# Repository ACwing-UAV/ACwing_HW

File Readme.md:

<p align="center">
  <picture>
    <source media="(prefers-color-scheme: dark)" srcset="https://raw.githubusercontent.com/ACwing-UAV/ACwing/main/brand/ACwing_logo_white.png">
    
  </picture>
</p>

<h1 align="center">ACwing – open drone flight hardware</h1>

<p align="center">
  STM32WB55 flight controller, 1S power board, GNSS and optical-flow expansions<br>
  KiCad 10 · JLCPCB-ready · by Andrea Cirillo
</p>

---

ACwing is a modular set of PCBs for small multirotors. This repository is the hardware part of the
[ACwing-UAV](https://github.com/ACwing-UAV) project: the firmware is in [ACwing_FW](https://github.com/ACwing-UAV/ACwing_FW),
the mechanics in [ACwing_Mechs](https://github.com/ACwing-UAV/ACwing_Mechs), and the
[ACwing](https://github.com/ACwing-UAV/ACwing) system repository pins the versions that belong together.

The core is a **universal flight controller** that talks to its
power stage through the common **4-in-1 ESC connector** (JST SH 8-pin): on the 1S indoor mini drone it sits on the
ACwing 1S power board; on a larger 3S–6S brushless drone the same FC runs with one or two commercial 20 × 20 4-in-1
ESCs. Two optional expansion boards plug into the FC's **Qwiic** (I2C) ports: a **GNSS + compass** board for outdoor
flight and an **optical-flow + ToF** board for indoor position and height hold.

## Boards

| Board | Rev | Size | Layers | What it does | Docs | KiCad |
|---|---|---|---|---|---|---|
| **ACwing FC** | A | 40 × 40 mm, 20 × 20 holes (grommets) | 4, 1.0 mm | flight controller, 1S–6S input, up to 8 motors, BLE | [FC docs](00%20-%20Docs/00%20-%20FC_Docs/) | [project](01%20-%20FC_KiCadProj/) |
| **ACwing ESC 1S** | A | 40 × 40 mm, 20 × 20 holes | 4, 1.0 mm | 1S power board: 4 brushed motor stages, current sensor, USB-C charger | [ESC docs](00%20-%20Docs/01%20-%20ESC_1S_Docs/) | [project](02%20-%20ESC_1S_KiCadProj/) |
| **ACwing GPS** | A | 30 × 30 mm, 20 × 20 holes | 2, 1.0 mm | GNSS (u-blox SAM-M10Q) + compass, stacked above the FC | [GPS docs](00%20-%20Docs/02%20-%20GPS_Docs/) | [project](03%20-%20GPS_KiCadProj/) |
| **ACwing Flow** | A | 21 × 25 mm, 2 × M2 | 2, 1.0 mm | optical flow (PMW3901) + ToF height (VL53L1X), under the frame | [Flow docs](00%20-%20Docs/03%20-%20FLOW_Docs/) | [project](04%20-%20FLOW_KiCadProj/) |

All boards are at **rev A**: no PCB has been produced yet. The revision letter moves to B with the first
change made after a board has been built and tested.

Every board folder in `00 - Docs` holds the schematic PDF, the BoM with costing, the JLCPCB BoM and pick-and-place
files, the Gerber zip, the DRC report, the STEP model and board views.

## System

```
              ┌─────────────────────────┐   Qwiic (J3)   ┌──────────────────┐
              │      ACwing FC rev A    │───────────────▶│  ACwing GPS rev A │  optional, outdoor
  USB-C ─────▶│ STM32WB55 · IMU · baro  │                └──────────────────┘
  ELRS RX ───▶│ compass · 16 MB flash   │   Qwiic (J4)   ┌──────────────────┐
              │ BLE · 4 × RGB LED       │───────────────▶│ ACwing Flow rev A │  indoor
              └───────┬─────────┬───────┘                └──────────────────┘
          ESC link A  │         │  ESC link B (motors 5–8)
         (JST SH 8)   ▼         ▼
   ┌──────────────────────┐   ┌──────────────────────────┐
   │ ACwing ESC 1S rev A  │ or│ commercial 4-in-1 ESC(s) │
   │ 1S, brushed, charger │   │ 2S–6S, brushless         │
   └──────────────────────┘   └──────────────────────────┘
```

**Stack (1S mini drone, Mech A1):** ESC 1S hard-mounted on the frame bosses → 5 mm → FC on M2 damping grommets →
6 mm → GPS board (optional). The flow board is mounted under the battery tray, sensor side down.

The interactive stack check (every part as a prism, every connector with a mated-plug envelope; 0 clashes) is in
[`04 - System_Docs/ACwing_stack_check.html`](00%20-%20Docs/04%20-%20System_Docs/) – download the folder and open the
page locally.

## Key features

**ACwing FC rev A**
- MCU **STM32WB55CGU6** (Cortex-M4 + M0+ radio core), BLE 5 with chip antenna and ST MLPF-WB55 front end.
- Sensors: **LSM6DSV16X** IMU, **LPS22HH** barometer, **IIS2MDC** compass; **W25Q128JV** 16 MB log flash.
- Input **1S–6S** (LM5166 buck, 3–65 V; 100 % duty cycle pass-through on 1S), 4.1 V system rail, 3.1 V and 3.31 V LDOs.
- **Two ESC links** (JST SH 8-pin, standard 4-in-1 pinout): 8 motor outputs (TIM2 / TIM1 / TIM16), VBAT and current
  sense from the ESC: the FC is supplied only through ESC link A (no battery pads).
- Two Qwiic ports, ELRS / CRSF UART port, USB-C (data, DFU, bench supply), 4 × addressable RGB LEDs (XL-2020, level-shifted data), SWD pogo grid.

**ACwing ESC 1S rev A**
- 4 brushed motor stages (AON7524 N-MOSFETs) for coreless 8520 motors, 470 µF bulk capacitor.
- 2 mΩ shunt + TSC213 current sense (0.1 V/A) on the ESC link.
- USB-C 1S charger (STC4054, 455 mA) with a charge switch that keeps FC and motors off while charging.
- Battery solder pads for a JST PH 2.0 pigtail.

**ACwing GPS rev A** – u-blox **SAM-M10Q** (integrated patch antenna, I2C/DDC) and **IIS2MDC** compass away from the
motor currents; Qwiic in / out on the top side, PPS LED, backup supply.

**ACwing Flow rev A** – PixArt **PMW3901MB** flow sensor behind an **STM32C011** I2C bridge, ST **VL53L1X** ToF;
Qwiic in / out; all parts on the sensor side.

## Repository structure

```
00 - Docs/
├── 00 - FC_Docs/         FC rev A: README, pin map, schematic, BoM, JLC files, Gerber, STEP, views
├── 01 - ESC_1S_Docs/     ESC 1S rev A: same set
├── 02 - GPS_Docs/        GPS rev A: same set
├── 03 - FLOW_Docs/       Flow rev A: same set + mechanical DXF
└── 04 - System_Docs/     mechanical handoff, preliminary-draft frame answer and reply, stack check (3D page and render)
01 - FC_KiCadProj/        KiCad project, library, 3D models, generator scripts
02 - ESC_1S_KiCadProj/
03 - GPS_KiCadProj/
04 - FLOW_KiCadProj/
```

Logos, silkscreen logo footprints and the brand and silkscreen tools are in
[`brand/`](https://github.com/ACwing-UAV/ACwing/tree/main/brand) of the ACwing system repository; each board keeps
a copy of the logo footprints it uses in its own project library.

## Ordering (JLCPCB)

For each board, from its docs folder:
1. Upload `<board>_gerber.zip` (1.0 mm FR-4; 4 layers for FC and ESC, 2 layers for GPS and Flow).
2. Enable assembly and upload `<board>_BoM_JLCPCB.xlsx` and `<board>_CPL.xlsx`. Every BoM line carries its LCSC part
   number; the CPL already includes the rotation corrections. Check the pin-1 marks in the JLC preview as listed in the
   board README ("To check before ordering").

Indicative component cost per board (10 / 100 boards, components only): FC 29.4 / 24.6 USD, ESC 1S 6.4 / 5.1 USD,
GPS 27.6 / 23.4 USD, Flow 11.1 / 9.4 USD. Check LCSC stock before ordering.

## Status

**Update 2026-11-08 (still rev A):** **all tracks on all four boards at 0 / 45 / 90°** (house routing rule; tool in
[`tools/route45`](tools/route45/)); FC battery pads J7 / J8 removed (the FC is supplied through ESC link A J2 pin 2 only);
ESC 1S J1 moved 0.77 mm to the front edge, the same edge distance as FC J2. See the
[mechanical handoff](00%20-%20Docs/04%20-%20System_Docs/ACwing_mechanical_handoff.md) §0.20. ESC 1S battery pads side by side across the rear-left corner. All
boards checked and saved with KiCad 10.0.6, all outputs, renders and the stack check page regenerated.

**Update 2026-11-07 evening (still rev A):** all boards **1.0 mm** again (JLC04101H-7628 on the 4-layer boards); FC ESC A
moved to the front-left, right above ESC 1S J1 (straight cable), ESC B to the old ESC A place; FC RGB LEDs at the corner tips
(same arrangement front and rear), battery pads and BLE antenna lower on the left edge, magnetometer and barometer right of
the MCU; ESC 1S charge port moved under the FC USB-C at the rear-right chamfer. See the [mechanical handoff](00%20-%20Docs/04%20-%20System_Docs/ACwing_mechanical_handoff.md) §0.19.

**Update 2026-11-07 (still rev A, superseded):** all boards **1.6 mm** thick (JLC04161H-7628 on the 4-layer boards, 1.51 mm core
on the 2-layer boards), KiCad 10 project files, outputs regenerated with KiCad 10; stack +1.8 mm, boards +4.2 g
(indoor set) / +5.2 g with the GPS. See the [mechanical handoff](00%20-%20Docs/04%20-%20System_Docs/ACwing_mechanical_handoff.md) §0.15.

**Update 2026-11-03 (still rev A):** plated M2 mounting holes with a GND copper ring on the ESC 1S, GPS and Flow
boards (as the FC); Flow SWD test pads moved to the back side (top edge, short SWD lines) and re-routed; silkscreen as edited by A. Cirillo.

**Update 2026-11-06 (still rev A):** ESC 1S link connector J1 moved to the front edge, under FC J2 (short ESC cable);
stack check of all inter-board cables in the [mechanical handoff](00%20-%20Docs/04%20-%20System_Docs/ACwing_mechanical_handoff.md) §0.14; new realistic renders of every board and of the stack.

**Layout and routing update 2026-11-02 (still rev A):** both FC ESC links on the front edge (ESC A next to ESC B,
ELRS moved to the rear edge); Qwiic IN / OUT on one edge on every board (GPS right edge, Flow top edge); no via in any
SMD pad (exposed thermal pads excepted); fine-pitch pads resized so every pad gap is ≥ 0.19 mm (JLCPCB mask dam),
board mask expansion 0.05 mm / minimum web 0.09 mm; CSP / BGA pads 0.25 mm; FC test pads TP1–TP8 in ascending order;
Flow test pads along the perimeter, symmetric; silkscreen reduced to connector labels, logos and board names. Board
files are now saved by KiCad 9 (KiCad 10 since 2026-11-07).

**Layout update 2026-10-24 (still rev A):** FC microcontroller at the board centre, ESC link B next to the ELRS port on
the front edge, input buck moved to the left edge (no longer between the rear LEDs), LED supply kept away from the
magnetometer (EMI check in the FC README); GPS Qwiic J1 aligned with FC J3.

All four boards are routed with **0 DRC violations and 0 unconnected pads** (KiCad 10, 2026-11-07). They are not built and tested
yet: see each board README for the bench checks planned before the first order (ERC in KiCad 8/9, power-stage tests,
land patterns to verify). Firmware: [ACwing_FW](https://github.com/ACwing-UAV/ACwing_FW).

## License

The ACwing hardware is open hardware, licensed under the
[CERN Open Hardware Licence Version 2 – Strongly Reciprocal](LICENSE) (**CERN-OHL-S-2.0**).
This covers the KiCad projects, schematics, layouts, Gerbers, BoMs, STEP models, renders and documentation.
The scripts in `tools/` and `99 - Tools/` are licensed under the [GNU GPL v3.0 or later](LICENSE-GPL-3.0).

You may use, study, modify, make and sell the boards. If you distribute modified designs, or products made from
them, you must make the modified sources available under the same licence.

Source location: <https://github.com/ACwing-UAV/ACwing_HW>

The ACwing name and logo identify the original project: you may keep them on unmodified boards, but please remove
them from modified designs so they are not mistaken for official ACwing hardware.

## Author

**Andrea Cirillo** – ACwing hardware design.

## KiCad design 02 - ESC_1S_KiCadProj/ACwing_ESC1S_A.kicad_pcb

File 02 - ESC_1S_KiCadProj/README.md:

# ACwing ESC 1S rev A – KiCad project

**Project:** ACwing · **Author:** Andrea Cirillo

KiCad sources of the ACwing ESC 1S rev A board (KiCad 10 project files, 2026-11-07). The board description, schematic PDF, BoM,
JLCPCB files, Gerber, STEP and board views are in [`00 - Docs/01 - ESC_1S_Docs`](../00%20-%20Docs/01%20-%20ESC_1S_Docs/).

| File / folder | What |
|---|---|
| `ACwing_ESC1S_A.kicad_pro`, `.kicad_sch`, `.kicad_pcb` | project, schematic, routed PCB |
| `*.kicad_sym`, `*.pretty/`, `fp-lib-table`, `sym-lib-table` | project library (symbols, footprints, ACwing logos) |
| `3d/` | STEP models, referenced as `${KIPRJMOD}/3d/...` |
| `generator/` | scripts that generated, routed and checked the design (build_all_esc.sh) |

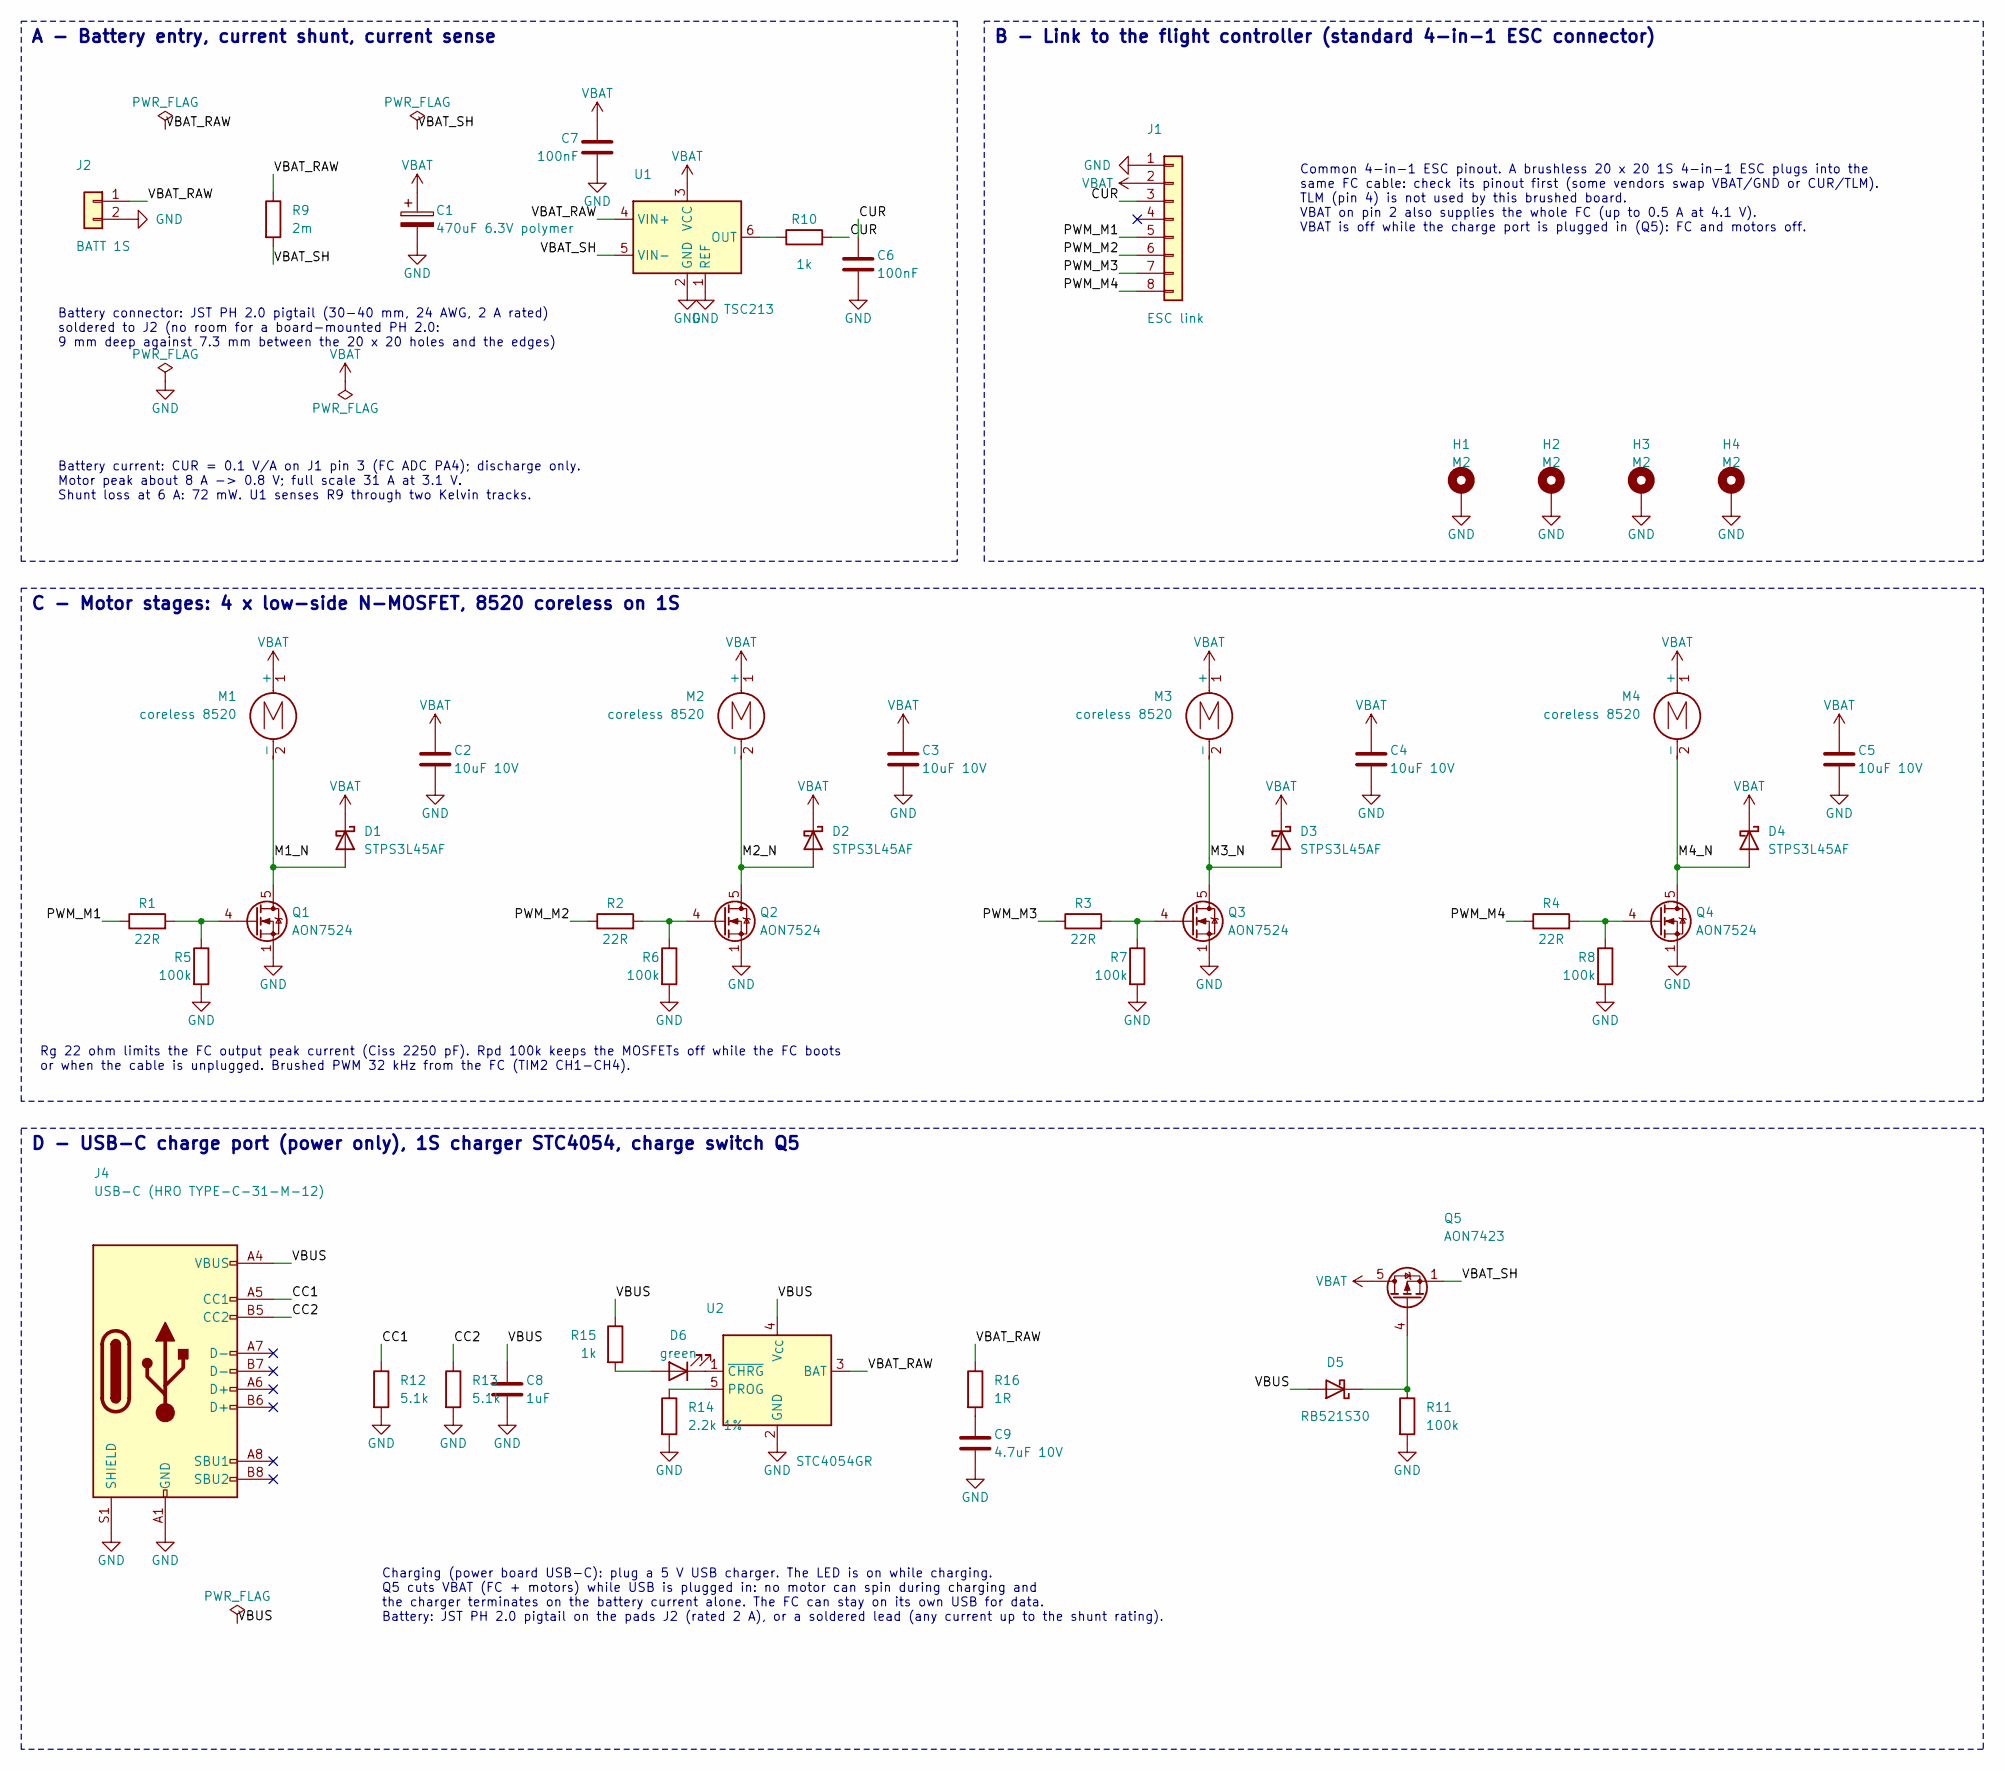
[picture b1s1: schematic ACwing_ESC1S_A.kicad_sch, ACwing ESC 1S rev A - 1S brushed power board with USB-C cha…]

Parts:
C1: 470uF 6.3V polymer; CP_EIA-7343-31_Kemet-D
C2, C3, C4, C5: 10uF 10V; C_0603_1608Metric
C6, C7: 100nF; C_0402_1005Metric
C8: 1uF; C_0402_1005Metric
C9: 4.7uF 10V; C_0603_1608Metric
D1, D2, D3, D4: STPS3L45AF; D_SMAflat
D5: RB521S30; D_SOD-523
D6: green; LED_0402_1005Metric
H1, H2, H3, H4: M2; MountingHole_PTH_2.2mm_M2_Pad3.6mm
J1: ESC link; JST_SH_SM08B-SRSS-TB_1x08-1MP_P1.00mm_Horizontal
J2: BATT 1S; BattPads_1x02_SMD
J4: USB-C (HRO TYPE-C-31-M-12); USB_C_Receptacle_HRO_TYPE-C-31-M-12
M1, M2, M3, M4: coreless 8520; MotorPads_1x02_SMD
Q1, Q2, Q3, Q4: AON7524; Vishay_PowerPAK_1212-8_Single
Q5: AON7423; Vishay_PowerPAK_1212-8_Single
R1, R2, R3, R4: 22R; R_0402_1005Metric
R5, R6, R7, R8, R11: 100k; R_0402_1005Metric
R9: 2m; R_1206_3216Metric
R10, R15: 1k; R_0402_1005Metric
R12, R13: 5.1k; R_0402_1005Metric
R14: 2.2k 1%; R_0402_1005Metric
R16: 1R; R_0402_1005Metric
U1: TSC213; SOT-363_SC-70-6
U2: STC4054GR; TSOT-23-5

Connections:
CC1: J4.A5 (CC1), R12.1
CC2: J4.B5 (CC2), R13.1
CUR: C6.1, J1.3, R10.2
GND: C1.2, C2.2, C3.2, C4.2, C5.2, C6.2, C7.2, C8.2, C9.2, H1.1, H2.1, H3.1, H4.1, J1.1, J2.2, J4.A1 (GND), J4.A12 (GND), J4.B1 (GND), J4.B12 (GND), J4.S1 (SHIELD), Q1.1 (S), Q1.2 (S), Q1.3 (S), Q2.1 (S), Q2.2 (S), Q2.3 (S), Q3.1 (S), Q3.2 (S), Q3.3 (S), Q4.1 (S), Q4.2 (S), Q4.3 (S), R5.2, R6.2, R7.2, R8.2, R11.2, R12.2, R13.2, R14.2, U1.1 (REF), U1.2 (GND), U2.2 (GND)
M1_N: D1.2 (A), M1.2 (-), Q1.5 (D)
M2_N: D2.2 (A), M2.2 (-), Q2.5 (D)
M3_N: D3.2 (A), M3.2 (-), Q3.5 (D)
M4_N: D4.2 (A), M4.2 (-), Q4.5 (D)
unnamed: C9.1, R16.2
unnamed: D5.1 (K), Q5.4 (G), R11.1
unnamed: D6.2 (A), R15.2
unnamed: D6.1 (K), U2.1 (~CHRG)
unnamed: Q1.4 (G), R1.2, R5.1
unnamed: Q2.4 (G), R2.2, R6.1
unnamed: Q3.4 (G), R3.2, R7.1
unnamed: Q4.4 (G), R4.2, R8.1
unnamed: R10.1, U1.6 (OUT)
unnamed: R14.1, U2.5 (PROG)
PWM_M1: J1.5, R1.1
PWM_M2: J1.6, R2.1
PWM_M3: J1.7, R3.1
PWM_M4: J1.8, R4.1
VBAT: C1.1, C2.1, C3.1, C4.1, C5.1, C7.1, D1.1 (K), D2.1 (K), D3.1 (K), D4.1 (K), J1.2, M1.1 (+), M2.1 (+), M3.1 (+), M4.1 (+), Q5.5 (D), U1.3 (VCC)
VBAT_RAW: J2.1, R9.1, R16.1, U1.4 (VIN+), U2.3 (BAT)
VBAT_SH: Q5.1 (S), Q5.2 (S), Q5.3 (S), R9.2, U1.5 (VIN-)
VBUS: C8.1, D5.2 (A), J4.A4 (VBUS), J4.A9 (VBUS), J4.B4 (VBUS), J4.B9 (VBUS), R15.1, U2.4 (V_{CC})

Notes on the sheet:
Common 4-in-1 ESC pinout. A brushless 20 x 20 1S 4-in-1 ESC plugs into the same FC cable: check its pinout first (some vendors swap VBAT/GND or CUR/TLM). TLM (pin 4) is not used by this brushed board. VBAT on pin 2 also supplies the whole FC (up to 0.5 A at 4.1 V). VBAT is off while the charge port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
C - Motor stages: 4 x low-side N-MOSFET, 8520 coreless on 1S
Charging (power board USB-C): plug a 5 V USB charger. The LED is on while charging. Q5 cuts VBAT (FC + motors) while USB is plugged in: no motor can spin during charging and the charger terminates on the battery current alone. The FC can stay on its own USB for data. Battery: JST PH 2.0 pigtail on 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
Battery connector: JST PH 2.0 pigtail (30-40 mm, 24 AWG, 2 A rated) soldered to J2 (no room for a board-mounted PH 2.0: 9 mm deep against 7.3 mm between the 20 x 20 holes and the edges)
Battery current: CUR = 0.1 V/A on J1 pin 3 (FC ADC PA4); discharge only. Motor peak about 8 A -> 0.8 V; full scale 31 A at 3.1 V. Shunt loss at 6 A: 72 mW. U1 senses R9 through two Kelvin tracks.
D - USB-C charge port (power only), 1S charger STC4054, charge switch Q5
A - Battery entry, current shunt, current sense
Rg 22 ohm limits the FC output peak current (Ciss 2250 pF). Rpd 100k keeps the MOSFETs off while the FC boots or when the cable is unplugged. Brushed PWM 32 kHz from the FC (TIM2 CH1-CH4).
B - Link to the flight controller (standard 4-in-1 ESC connector)

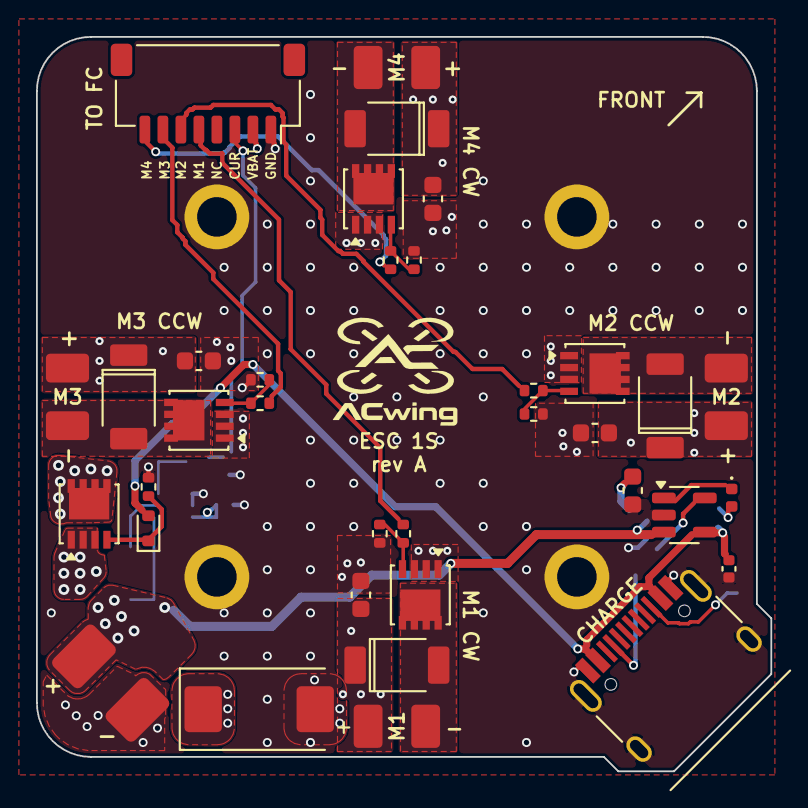
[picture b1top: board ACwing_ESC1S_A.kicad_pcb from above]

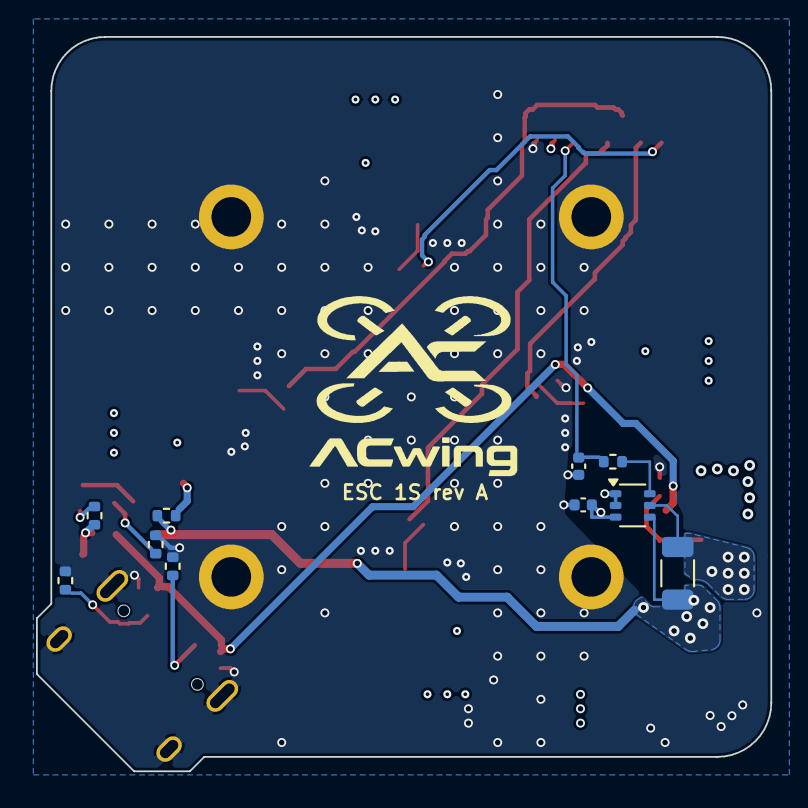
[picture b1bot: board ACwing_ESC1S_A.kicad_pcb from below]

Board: 4 copper layers, 40.8 x 40.8 mm, 51 parts (11 on the bottom side), 26 nets.

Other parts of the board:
LOGO1: ACwing_Logo_Full_6mm
LOGO2: ACwing_Logo_Full_10mm

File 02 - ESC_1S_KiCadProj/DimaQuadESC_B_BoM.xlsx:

DimaQuadESC rev B - assembly BoM (1 board)
Source: DimaQuadESC_B.kicad_sch / DimaQuadESC_B.kicad_pcb. LCSC part numbers fr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
Item | Quantity | Part Reference | Value | MPN | Manufacturer | LCSC / JLCPCB # | Package | Description | Side | Notes
1 | 1 | C1 | 470uF 6.3V polymer | T520D477M006ATE015 | KEMET | C696809 | 7343-31 (EIA D), h 2.8 mm | Capacitor, tantalum polymer, 470 uF, 6.3 V, 15 mOhm | Top | Bulk at the battery entry, + to VBAT. Low LCSC stock: any 470 uF 6.3 V 7343 pol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
2 | 4 | C2, C3, C4, C5 | 10uF 10V | CL10A106KP8NNNC | Samsung Electro-Mechanics | C19702 | 0603 (1608 metric) | Capacitor, MLCC, 10 uF, 10 V, X5R | Top | Local decoupling next to each MOSFET (hot loop)
3 | 2 | C6, C7 | 100nF | CL05B104KO5NNNC | Samsung Electro-Mechanics | C1525 | 0402 (1005 metric) | Capacitor, MLCC, 100 nF, 16 V, X7R | Bottom | U1 supply (C7) and CUR filter (C6)
4 | 1 | C8 | 1uF | CL05A105KA5NQNC | Samsung Electro-Mechanics | C52923 | 0402 (1005 metric) | Capacitor, MLCC, 1 uF, 25 V, X5R | Top | Charger input (VBUS)
5 | 1 | C9 | 4.7uF 10V | CL10A475KO8NNNC | Samsung Electro-Mechanics | C19666 | 0603 (1608 metric) | Capacitor, MLCC, 4.7 uF, 16 V, X5R | Top | Charger output RC (with R16)
6 | 4 | D1, D2, D3, D4 | STPS3L45AF | SS34F | GOODWORK | C908669 | SMAF (DO-221AC) | Diode, Schottky, 40 V, 3 A, Vf 0.55 V @ 3 A | Top | Motor freewheel diode. Replaces STPS3L45AF (low LCSC stock), same DO-221AC outl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
7 | 1 | D5 | RB521S30 | RB521S30T1G | onsemi | C8523 | SOD-523 | Diode, Schottky, 30 V, 200 mA | Top | VBUS -> Q5 gate (charge switch off while charging)
8 | 1 | D6 | green | XL-1005UGC | XINGLIGHT | C965793 | 0402 (1005 metric) | LED, green 525 nm, 0402 | Top | Charge LED (on = charging), top side next to the charge port
9 | 1 | J1 | ESC link | SM08B-SRSS-TB(LF)(SN) | JST | C160407 | JST SH 8P side entry, h 2.9 mm | Connector, JST SH, 8 positions, 1.0 mm pitch, side entry | Top | ESC link to the FC: 1 GND, 2 VBAT, 3 CUR, 4 TLM (n.c.), 5-8 M1-M4. Mouth at the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
10 | 1 | J4 | USB-C (HRO TYPE-C-31-M-12) | TYPE-C-31-M-12 | HRO (Korea Hroparts) | C165948 | USB-C receptacle, 16 pin, SMD + THT shell | Connector, USB Type-C receptacle, top mount | Top | Charge port (power only), front-left chamfer
11 | 4 | Q1, Q2, Q3, Q4 | AON7524 | AON7524 | Alpha & Omega Semiconductor | C431195 | DFN 3x3 EP (DFN3x3A_8L_EP1) | MOSFET, N-channel, 30 V, 30 A, logic level | Top | Low-side motor switch, one per channel. Land pattern: Vishay PowerPAK 1212-8 (c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
12 | 1 | Q5 | AON7423 | AON7423 | Alpha & Omega Semiconductor | C99711 | DFN 3x3 EP | MOSFET, P-channel, 20 V, 50 A, 4.9 mOhm @ -2.5 V, Vgs +-8 V | Top | Charge switch Q5: board supply off while the charge port is plugged in
13 | 4 | R1, R2, R3, R4 | 22R | 0402WGF220JTCE | UNI-ROYAL | C25092 | 0402 (1005 metric) | Resistor, 22 Ohm, 5 %, 1/16 W | Top | MOSFET gate resistors
14 | 5 | R5, R6, R7, R8, R11 | 100k | 0402WGF1003TCE | UNI-ROYAL | C25741 | 0402 (1005 metric) | Resistor, 100 kOhm, 1 %, 1/16 W | Top | Gate pull-downs: MOSFETs off with the cable unplugged or the FC booting (R5-R8)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
15 | 1 | R9 | 2m | RLM12FTCMR002 | TA-I Tech | C710257 | 1206 (3216 metric) | Resistor, current sense, 2 mOhm, 1 %, 1 W | Bottom | Battery shunt, bottom side, Kelvin-connected to U1
16 | 2 | R10, R15 | 1k | 0402WGF1001TCE | UNI-ROYAL | C11702 | 0402 (1005 metric) | Resistor, 1 kOhm, 1 %, 1/16 W | Bottom | CUR filter (1k / 100 nF, 1.6 kHz) (R10); charge LED (R15)
17 | 2 | R12, R13 | 5.1k | 0402WGF5101TCE | UNI-ROYAL | C25905 | 0402 (1005 metric) | Resistor, 5.1 kOhm, 1 %, 1/16 W | Bottom | USB-C CC pull-downs (sink)
18 | 1 | R14 | 2.2k 1% | 0402WGF2201TCE | UNI-ROYAL | C25879 | 0402 (1005 metric) | Resistor, 2.2 kOhm, 1 %, 1/16 W | Bottom | Charger R_PROG: 455 mA
19 | 1 | R16 | 1R | FRC0402F1R00TS | FOJAN | C2909329 | 0402 (1005 metric) | Resistor, 1 Ohm, 1 %, 1/16 W | Bottom | Charger output RC (with C9)
20 | 1 | U1 | TSC213 | TSC213ICT | STMicroelectronics | C1858319 | SC70-6 (SOT-363) | Current-sense amplifier, gain 50 V/V, zero drift | Bottom | Battery current: CUR = 0.1 V/A on J1 pin 3
21 | 1 | U2 | STC4054GR | STC4054GR | STMicroelectronics | C262930 | TSOT-23-5 | Li-ion linear charger, 4.2 V, up to 800 mA | Top | 1S charger, 455 mA (R14 2.2k)
Total | 40 | Total placements (assembled parts) | - | 21 | line items | - | - | - | - | Not-assembled items listed below
Not assembled (PCB features / DNP)
Item | Quantity | Part Reference | Value | MPN | Manufacturer | LCSC / JLCPCB # | Package | Description | Side | Notes
NA1 | 4 | H1, H2, H3, H4 | M2 | N/A (PCB feature) | N/A | N/A | NPTH 2.2 mm | Mounting hole, M2, 20 x 20 pattern | Top | Hard mount to the frame bosses; keep-out r 2.6 mm on both sides
NA2 | 4 | M1, M2, M3, M4 | coreless 8520 | N/A (PCB feature) | N/A | N/A | MotorPads_1x02_SMD | Motor lead solder pads (8.5 x 20 mm coreless brushed motors, 3.7 V) | Top | Soldered by hand; "+" pad (silk mark) to the red/blue lead. M1/M4 CW, M2/M3 CCW
NA3 | 1 | J2 | BATT 1S | N/A (PCB feature) | N/A | N/A | BattPads_1x02_SMD | Battery lead solder pads, 1S LiPo, AWG 22-24 | Top | Rear corner; "+" silk mark on the VBAT pad
NA4 | 1 | - (soldered to J2) | JST PH 2.0 pigtail | PH 2.0 male lead, 30-40 mm, 24 AWG (any brand) | N/A | N/A | off-board | Battery plug pigtail soldered to J2 (rated 2 A) | Top | Hand-soldered: red to +. Match the polarity of the battery plug (not standardis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

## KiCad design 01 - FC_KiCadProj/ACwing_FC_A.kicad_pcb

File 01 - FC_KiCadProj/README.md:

# ACwing FC rev A – KiCad project

**Project:** ACwing · **Author:** Andrea Cirillo

KiCad sources of the ACwing FC rev A board (KiCad 10 project files, 2026-11-07). The board description, schematic PDF, BoM,
JLCPCB files, Gerber, STEP and board views are in [`00 - Docs/00 - FC_Docs`](../00%20-%20Docs/00%20-%20FC_Docs/).

| File / folder | What |
|---|---|
| `ACwing_FC_A.kicad_pro`, `.kicad_sch`, `.kicad_pcb` | project, schematic, routed PCB |
| `*.kicad_sym`, `*.pretty/`, `fp-lib-table`, `sym-lib-table` | project library (symbols, footprints, ACwing logos) |
| `3d/` | STEP models, referenced as `${KIPRJMOD}/3d/...` |
| `generator/` | scripts that generated, routed and checked the design (build_all_h.sh) |

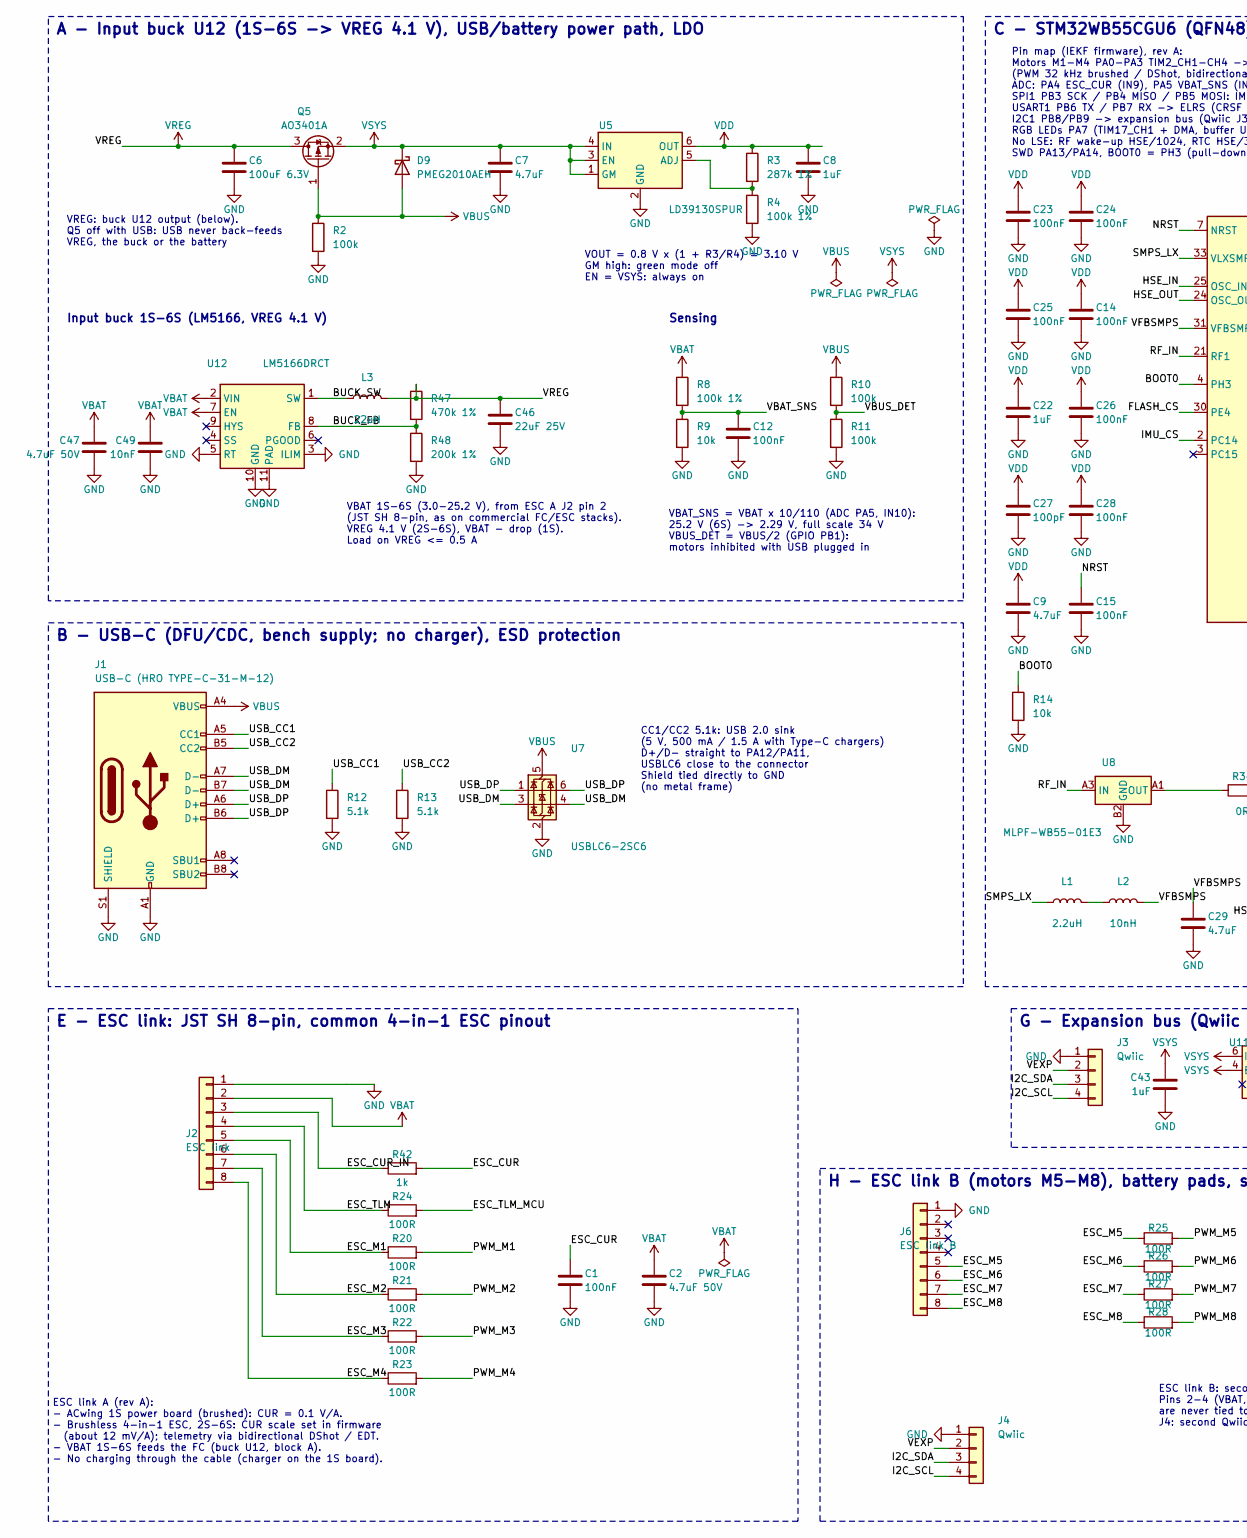
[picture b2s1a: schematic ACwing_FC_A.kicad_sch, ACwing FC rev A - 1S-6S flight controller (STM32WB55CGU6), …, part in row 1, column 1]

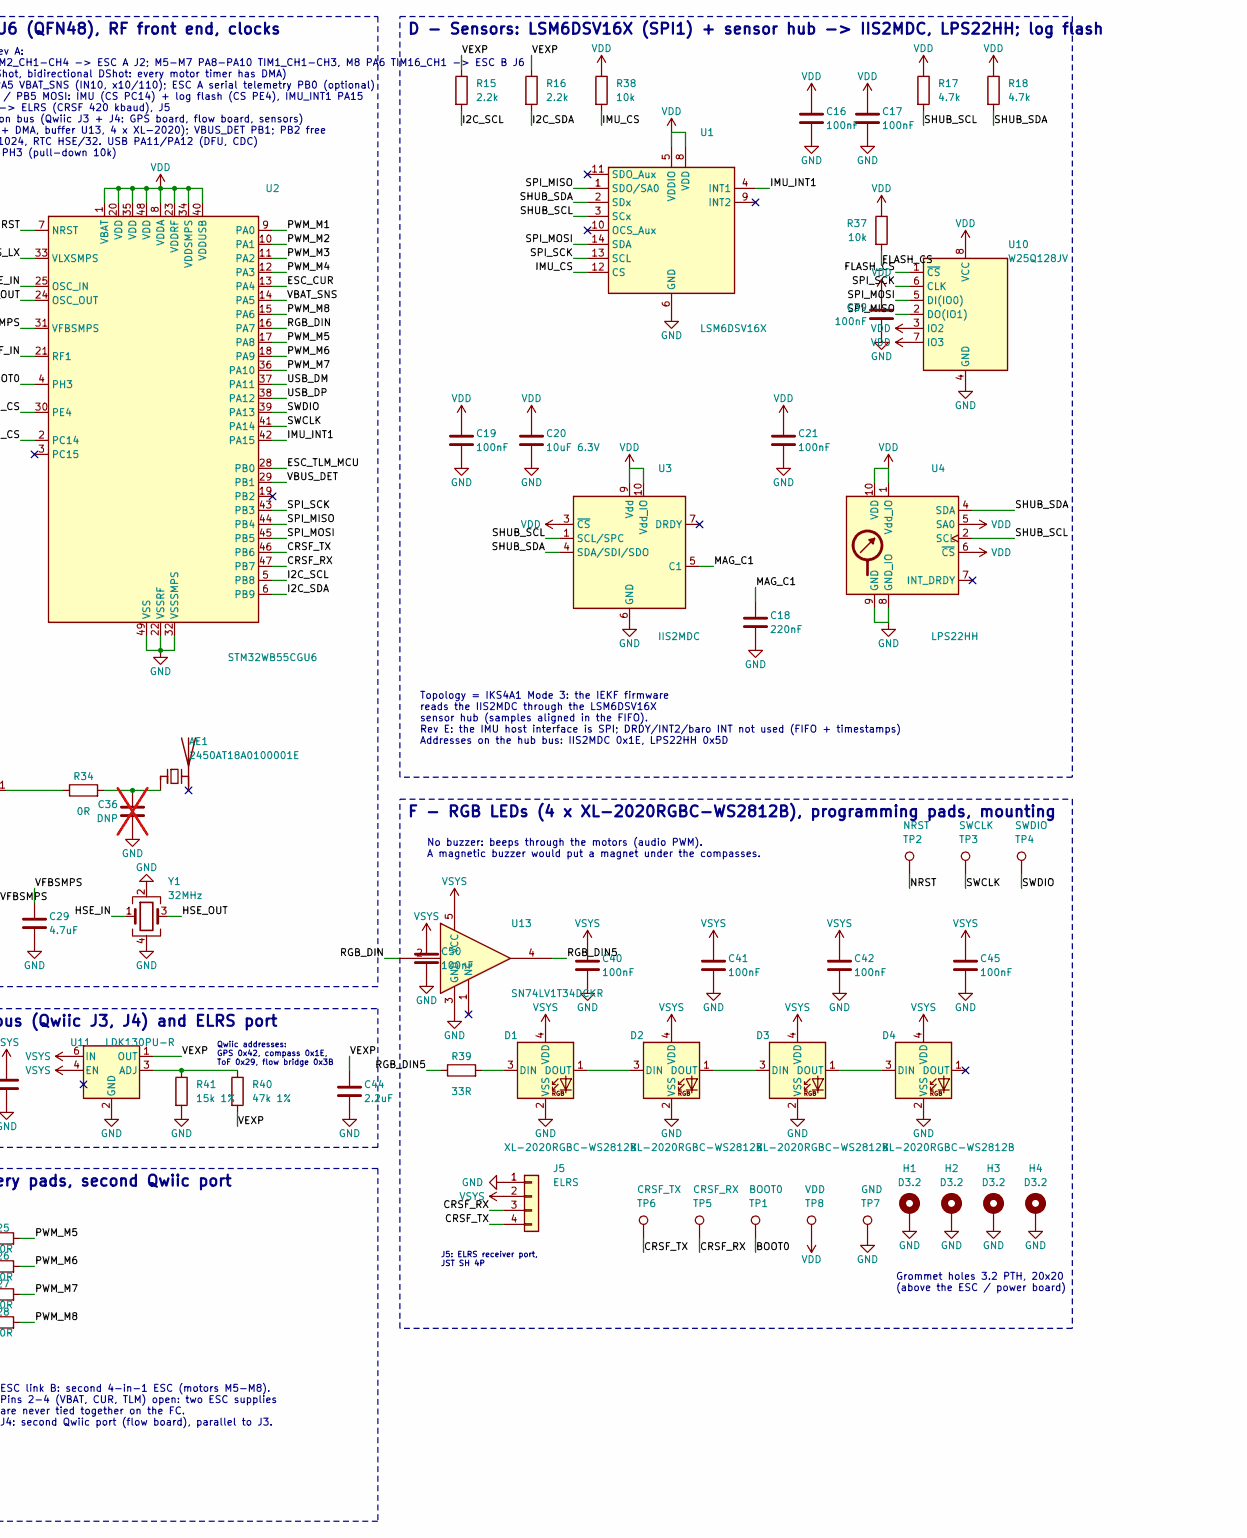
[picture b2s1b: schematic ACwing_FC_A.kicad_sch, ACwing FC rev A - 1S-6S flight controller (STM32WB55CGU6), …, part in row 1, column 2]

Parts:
AE1: 2450AT18A0100001E; Johanson_2450AT18x100
C1, C12, C14, C15, C16, C17, C19, C21, C23, C24, C25, C26, C28, C39, C40, C41, C42, C45, C50: 100nF; C_0402_1005Metric
C2, C47: 4.7uF 50V; C_1206_3216Metric
C6: 100uF 6.3V; C_1206_3216Metric
C7, C9: 4.7uF; C_0603_1608Metric
C8, C22, C43: 1uF; C_0402_1005Metric
C18: 220nF; C_0402_1005Metric
C20: 10uF 6.3V; C_0603_1608Metric
C27: 100pF; C_0402_1005Metric
C29: 4.7uF; C_0402_1005Metric
C36: DNP; C_0402_1005Metric; not fitted
C44: 2.2uF; C_0402_1005Metric
C46: 22uF 25V; C_0805_2012Metric
C49: 10nF; C_0402_1005Metric
D1, D2, D3, D4: XL-2020RGBC-WS2812B; LED_WS2812B-2020_PLCC4_2.0x2.0mm
D9: PMEG2010AEH; D_SOD-123F
H1, H2, H3, H4: D3.2; Grommet_PTH_3.2mm_Pad5.0mm
J1: USB-C (HRO TYPE-C-31-M-12); USB_C_Receptacle_HRO_TYPE-C-31-M-12
J2: ESC link; JST_SH_SM08B-SRSS-TB_1x08-1MP_P1.00mm_Horizontal
J3, J4: Qwiic; JST_SH_SM04B-SRSS-TB_1x04-1MP_P1.00mm_Horizontal
J5: ELRS; JST_SH_SM04B-SRSS-TB_1x04-1MP_P1.00mm_Horizontal
J6: ESC link B; JST_SH_SM08B-SRSS-TB_1x08-1MP_P1.00mm_Horizontal
L1: 2.2uH; L_0805_2012Metric
L2: 10nH; L_0402_1005Metric
L3: 22uH; L_Sunlord_SWPA5040S
Q5: AO3401A; SOT-23
R2, R10, R11: 100k; R_0402_1005Metric
R3: 287k 1%; R_0402_1005Metric
R4, R8: 100k 1%; R_0402_1005Metric
R9, R14, R37, R38: 10k; R_0402_1005Metric
R12, R13: 5.1k; R_0402_1005Metric
R15, R16: 2.2k; R_0402_1005Metric
R17, R18: 4.7k; R_0402_1005Metric
R20, R21, R22, R23, R24, R25, R26, R27, R28: 100R; R_0402_1005Metric
R34: 0R; R_0402_1005Metric
R39: 33R; R_0402_1005Metric
R40: 47k 1%; R_0402_1005Metric
R41: 15k 1%; R_0402_1005Metric
R42: 1k; R_0402_1005Metric
R47: 470k 1%; R_0402_1005Metric
R48: 200k 1%; R_0402_1005Metric
TP1: BOOT0; TestPoint_Pad_D1.0mm
TP2: NRST; TestPoint_Pad_D1.0mm
TP3: SWCLK; TestPoint_Pad_D1.0mm
TP4: SWDIO; TestPoint_Pad_D1.0mm
TP5: CRSF_RX; TestPoint_Pad_D1.0mm
TP6: CRSF_TX; TestPoint_Pad_D1.0mm
TP7: GND; TestPoint_Pad_D1.0mm
TP8: VDD; TestPoint_Pad_D1.0mm
U1: LSM6DSV16X; LGA-14_3x2.5mm_P0.5mm_LayoutBorder3x4y
U2: STM32WB55CGU6; QFN-48-1EP_7x7mm_P0.5mm_EP5.6x5.6mm
U3: IIS2MDC; LGA-12_2x2mm_P0.5mm
U4: LPS22HH; ST_HLGA-10_2x2mm_P0.5mm_LayoutBorder3x2y
U5: LD39130SPUR; DFN-6_1.3x1.2mm_P0.4mm
U7: USBLC6-2SC6; SOT-23-6
U8: MLPF-WB55-01E3; ST_MLPF-WB55-01E3_CSP-6
U10: W25Q128JV; WSON-8-1EP_6x5mm_P1.27mm_EP3.4x4mm
U11: LDK130PU-R; DFN-6_1.3x1.2mm_P0.4mm
U12: LM5166DRCT; Texas_DRC0010J
U13: SN74LV1T34DCKR; SOT-353_SC-70-5
Y1: 32MHz; Crystal_SMD_2016-4Pin_2.0x1.6mm

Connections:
BOOT0: R14.1, TP1.1, U2.4 (PH3)
BUCK_FB: R47.2, R48.1, U12.8 (FB)
BUCK_SW: L3.1, U12.1 (SW)
CRSF_RX: J5.3, TP5.1, U2.47 (PB7)
CRSF_TX: J5.4, TP6.1, U2.46 (PB6)
ESC_CUR: C1.1, R42.2, U2.13 (PA4)
ESC_CUR_IN: J2.3, R42.1
ESC_M1: J2.5, R20.1
ESC_M2: J2.6, R21.1
ESC_M3: J2.7, R22.1
ESC_M4: J2.8, R23.1
ESC_M5: J6.5, R25.1
ESC_M6: J6.6, R26.1
ESC_M7: J6.7, R27.1
ESC_M8: J6.8, R28.1
ESC_TLM: J2.4, R24.1
ESC_TLM_MCU: R24.2, U2.28 (PB0)
FLASH_CS: R37.2, U2.30 (PE4), U10.1 (~CS)
GND: C1.2, C2.2, C6.2, C7.2, C8.2, C9.2, C12.2, C14.2, C15.2, C16.2, C17.2, C18.2, C19.2, C20.2, C21.2, C22.2, C23.2, C24.2, C25.2, C26.2, C27.2, C28.2, C29.2, C36.2, C39.2, C40.2, C41.2, C42.2, C43.2, C44.2, C45.2, C46.2, C47.2, C49.2, C50.2, D1.2 (VSS), D2.2 (VSS), D3.2 (VSS), D4.2 (VSS), H1.1, H2.1, H3.1, H4.1, J1.A1 (GND), J1.A12 (GND), J1.B1 (GND), J1.B12 (GND), J1.S1 (SHIELD), J2.1, J3.1, J4.1, J5.1, J6.1, R2.2, R4.2, R9.2, R11.2, R12.2, R13.2, R14.2, R41.2, R48.2, TP7.1, U1.6 (GND), U1.7 (GND), U2.22 (VSSRF), U2.32 (VSSSMPS), U2.49 (VSS), U3.6 (GND), U3.8 (GND), U4.3 (GND), U4.8 (GND_IO), U4.9 (GND), U5.2 (GND), U7.2 (GND), U8.A2 (GND), U8.B1 (GND), U8.B2 (GND), U8.B3 (GND), U10.4 (GND), U11.2 (GND), U12.3 (ILIM), U12.5 (RT), U12.10 (GND), U12.11 (PAD), U13.3 (GND), Y1.2, Y1.4
HSE_IN: U2.25 (OSC_IN), Y1.1
HSE_OUT: U2.24 (OSC_OUT), Y1.3
I2C_SCL: J3.4, J4.4, R15.2, U2.5 (PB8)
I2C_SDA: J3.3, J4.3, R16.2, U2.6 (PB9)
IMU_CS: R38.2, U1.12 (CS), U2.2 (PC14)
IMU_INT1: U1.4 (INT1), U2.42 (PA15)
MAG_C1: C18.1, U3.5 (C1)
NRST: C15.1, TP2.1, U2.7 (NRST)
unnamed: AE1.1 (FEED), C36.1, R34.2
unnamed: D1.3 (DIN), R39.2
unnamed: D1.1 (DOUT), D2.3 (DIN)
unnamed: D2.1 (DOUT), D3.3 (DIN)
unnamed: D3.1 (DOUT), D4.3 (DIN)
unnamed: L1.2, L2.1
unnamed: R3.2, R4.1, U5.5 (ADJ)
unnamed: R34.1, U8.A1 (OUT)
unnamed: R40.1, R41.1, U11.3 (ADJ)
PWM_M1: R20.2, U2.9 (PA0)
PWM_M2: R21.2, U2.10 (PA1)
PWM_M3: R22.2, U2.11 (PA2)
PWM_M4: R23.2, U2.12 (PA3)
PWM_M5: R25.2, U2.17 (PA8)
PWM_M6: R26.2, U2.18 (PA9)
PWM_M7: R27.2, U2.36 (PA10)
PWM_M8: R28.2, U2.15 (PA6)
RF_IN: U2.21 (RF1), U8.A3 (IN)
RGB_DIN: U2.16 (PA7), U13.2
RGB_DIN5: R39.1, U13.4
SHUB_SCL: R17.2, U1.3 (SCx), U3.1 (SCL/SPC), U4.2 (SCL)
SHUB_SDA: R18.2, U1.2 (SDx), U3.4 (SDA/SDI/SDO), U4.4 (SDA)
SMPS_LX: L1.1, U2.33 (VLXSMPS)
SPI_MISO: U1.1 (SDO/SA0), U2.44 (PB4), U10.2 (DO(IO1))
SPI_MOSI: U1.14 (SDA), U2.45 (PB5), U10.5 (DI(IO0))
SPI_SCK: U1.13 (SCL), U2.43 (PB3), U10.6 (CLK)
SWCLK: TP3.1, U2.41 (PA14)
SWDIO: TP4.1, U2.39 (PA13)
USB_CC1: J1.A5 (CC1), R12.1
USB_CC2: J1.B5 (CC2), R13.1
USB_DM: J1.A7 (D-), J1.B7 (D-), U2.37 (PA11), U7.3 (I/O2), U7.4 (I/O2)
USB_DP: J1.A6 (D+), J1.B6 (D+), U2.38 (PA12), U7.1 (I/O1), U7.6 (I/O1)
VBAT: C2.1, C47.1, C49.1, J2.2, R8.1, U12.2 (VIN), U12.7 (EN)
VBAT_SNS: C12.1, R8.2, R9.1, U2.14 (PA5)
VBUS: D9.2 (A), J1.A4 (VBUS), J1.A9 (VBUS), J1.B4 (VBUS), J1.B9 (VBUS), Q5.1 (G), R2.1, R10.1, U7.5 (VBUS)
VBUS_DET: R10.2, R11.1, U2.29 (PB1)
VDD: C8.1, C9.1, C14.1, C16.1, C17.1, C19.1, C20.1, C21.1, C22.1, C23.1, C24.1, C25.1, C26.1, C27.1, C28.1, C39.1, R3.1, R17.1, R18.1, R37.1, R38.1, TP8.1, U1.5 (VDDIO), U1.8 (VDD), U2.1 (VBAT), U2.8 (VDDA), U2.20 (VDD), U2.23 (VDDRF), U2.34 (VDDSMPS), U2.35 (VDD), U2.40 (VDDUSB), U2.48 (VDD), U3.3 (~CS), U3.9 (Vdd), U3.10 (Vdd_IO), U4.1 (Vdd_IO), U4.5 (SA0), U4.6 (~CS), U4.10 (VDD), U5.6 (OUT), U10.3 (IO2), U10.7 (IO3), U10.8 (VCC)
VEXP: C44.1, J3.2, J4.2, R15.1, R16.1, R40.2, U11.1 (OUT)
VFBSMPS: C29.1, L2.2, U2.31 (VFBSMPS)
VREG: C6.1, C46.1, L3.2, Q5.3 (D), R47.1
VSYS: C7.1, C40.1, C41.1, C42.1, C43.1, C45.1, C50.1, D1.4 (VDD), D2.4 (VDD), D3.4 (VDD), D4.4 (VDD), D9.1 (K), J5.2, Q5.2 (S), U5.1 (GM), U5.3 (EN), U5.4 (IN), U11.4 (EN), U11.6 (IN), U13.5 (VCC)

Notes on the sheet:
ESC link B: second 4-in-1 ESC (motors M5-M8). Pins 2-4 (VBAT, CUR, TLM) open: two ESC supplies are never tied together on the FC. J4: second Qwiic port (flow board), parallel to J3.
F - RGB LEDs (4 x XL-2020RGBC-WS2812B), programming pads, mounting
VOUT = 0.8 V x (1 + R3/R4) = 3.10 V GM high: green mode off EN = VSYS: always on
A - Input buck U12 (1S-6S -> VREG 4.1 V), USB/battery power path, LDO
ESC link A (rev A): - ACwing 1S power board (brushed): CUR = 0.1 V/A. - Brushless 4-in-1 ESC, 2S-6S: CUR scale set in firmware (about 12 mV/A); telemetry via bidirectional DShot / EDT. - VBAT 1S-6S feeds the FC (buck U12, block A). - No charging through the cable (charger on the 1S board).
Grommet holes 3.2 PTH, 20x20 (above the ESC / power board)
B - USB-C (DFU/CDC, bench supply; no charger), ESD protection
D - Sensors: LSM6DSV16X (SPI1) + sensor hub -> IIS2MDC, LPS22HH; log flash
Pin map (IEKF firmware), rev A: Motors M1-M4 PA0-PA3 TIM2_CH1-CH4 -> ESC A J2; M5-M7 PA8-PA10 TIM1_CH1-CH3, M8 PA6 TIM16_CH1 -> ESC B J6 (PWM 32 kHz brushed / DShot, bidirectional DShot: every motor timer has DMA) ADC: PA4 ESC_CUR (IN9), PA5 VBAT_SNS (IN10, x10/110); ESC A serial telemetry PB0 (opt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
VBAT_SNS = VBAT x 10/110 (ADC PA5, IN10): 25.2 V (6S) -> 2.29 V, full scale 34 V VBUS_DET = VBUS/2 (GPIO PB1): motors inhibited with USB plugged in
Qwiic addresses: GPS 0x42, compass 0x1E, ToF 0x29, flow bridge 0x3B
J5: ELRS receiver port, JST SH 4P
Sensing
VREG: buck U12 output (below). Q5 off with USB: USB never back-feeds VREG, the buck or the battery
H - ESC link B (motors M5-M8), battery pads, second Qwiic port
No buzzer: beeps through the motors (audio PWM). A magnetic buzzer would put a magnet under the compasses.
E - ESC link: JST SH 8-pin, common 4-in-1 ESC pinout
C - STM32WB55CGU6 (QFN48), RF front end, clocks
CC1/CC2 5.1k: USB 2.0 sink (5 V, 500 mA / 1.5 A with Type-C chargers) D+/D- straight to PA12/PA11, USBLC6 close to the connector Shield tied directly to GND (no metal frame)
Topology = IKS4A1 Mode 3: the IEKF firmware reads the IIS2MDC through the LSM6DSV16X sensor hub (samples aligned in the FIFO). Rev E: the IMU host interface is SPI; DRDY/INT2/baro INT not used (FIFO + timestamps) Addresses on the hub bus: IIS2MDC 0x1E, LPS22HH 0x5D
VBAT 1S-6S (3.0-25.2 V), from ESC A J2 pin 2 (JST SH 8-pin, as on commercial FC/ESC stacks). VREG 4.1 V (2S-6S), VBAT - drop (1S). Load on VREG <= 0.5 A
G - Expansion bus (Qwiic J3, J4) and ELRS port
Input buck 1S-6S (LM5166, VREG 4.1 V)
